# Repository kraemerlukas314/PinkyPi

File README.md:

# PinkyPi
Ortho Staggered ergo split keyboard using Raspberry Pi Pico \
\
 \
\

# Flash CircuitPython firmware:
0. Connect Pico to PC while holding down the "Bootsel" button
1. Open Thonny
2. Go to: Tools -> Options -> Interpreter
3. Choose CircuitPython (RP2040)
4. Click on "Install or update CircuitPython"
5. Rest is self-explanatory, firmware version 9.0.5 is recommended (code is only tested on this version)

# Run the keyboard code:
1. Flash CircuitPython firmware
2. copy "lib" folder of this repo to the Picos internal storage
3. Open Thonny
4. Execute the actual .py code file
5. (rename file to main if it should run automatically on Pico startup)

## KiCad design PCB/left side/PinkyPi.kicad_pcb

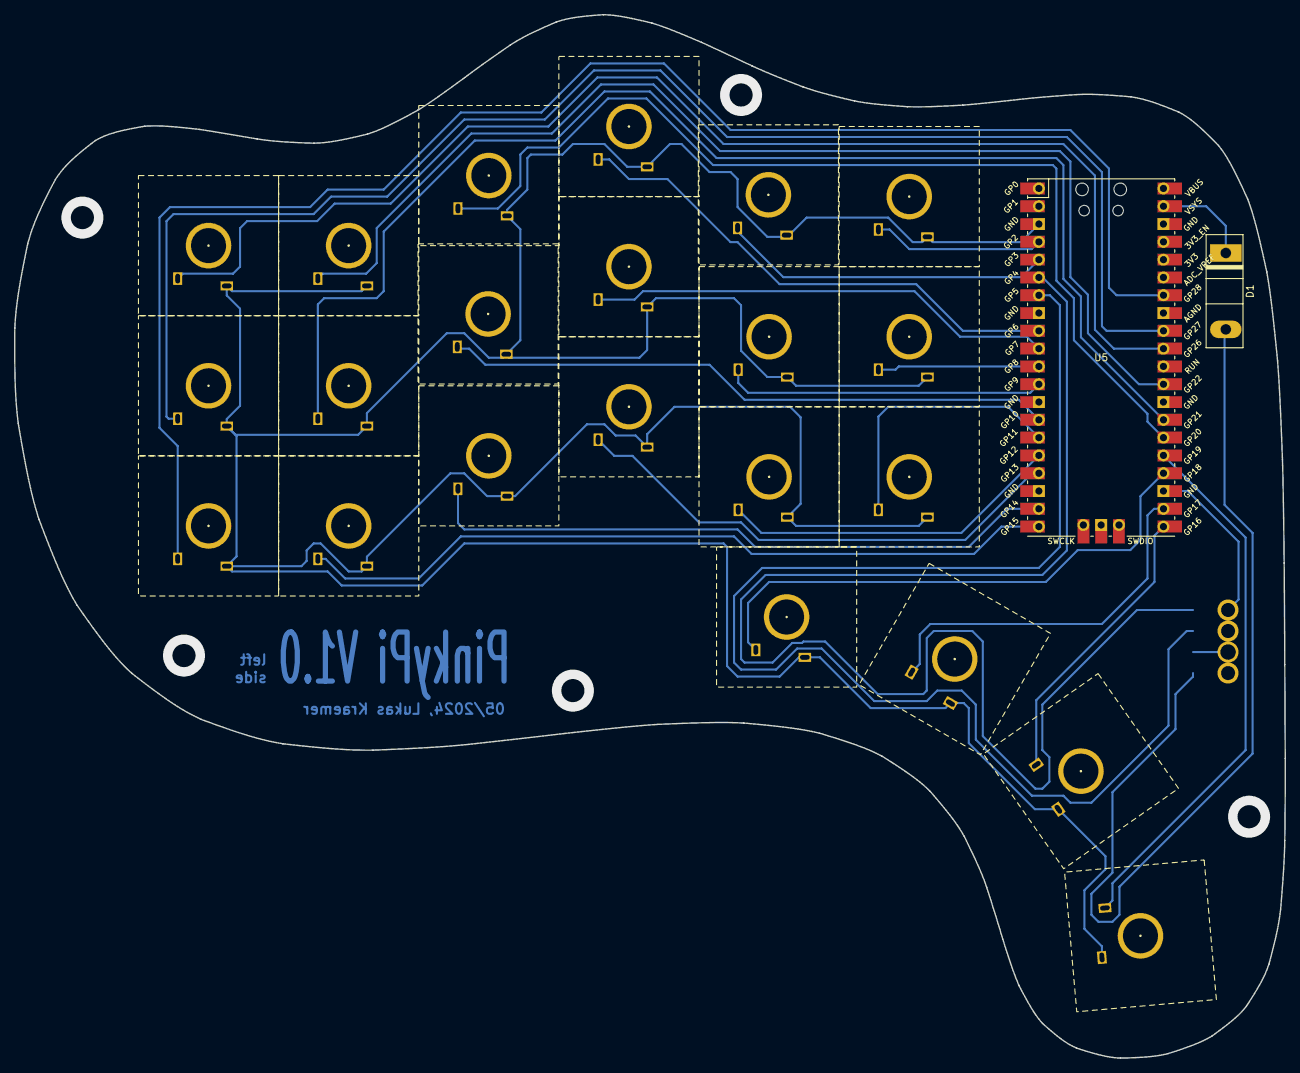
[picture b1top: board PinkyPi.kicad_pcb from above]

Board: 2 copper layers, 181.3 x 148.9 mm, 25 parts (0 on the bottom side), 27 nets.

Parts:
D1: STBR3008WY; D_DO-247_Vertical
U1, U2, U3, U4, U6, U7, U8, U9, U10, U11, U12, U13, U14, U15, U16, U17, U18, U19, U20, U21, U22, U24: Gateron Switch Footprint
U5: Pico; RPi_Pico_SMD_TH
U23: Communication Port

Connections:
/L1: U1.2 (OUT), U5.4 (GPIO2)
/L2: U5.5 (GPIO3), U7.2 (OUT)
/L3: U5.9 (GPIO6), U12.2 (OUT)
/L4: U2.2 (OUT), U5.10 (GPIO7)
/L5: U5.11 (GPIO8), U8.2 (OUT)
/L6: U5.12 (GPIO9), U13.2 (OUT)
/L7: U5.32 (GPIO27_ADC1), U18.2 (OUT)
/L8: U5.14 (GPIO10), U9.2 (OUT)
/L9: U5.15 (GPIO11), U14.2 (OUT)
/L10: U4.2 (OUT), U5.16 (GPIO12)
/L11: U5.17 (GPIO13), U10.2 (OUT)
/L12: U5.34 (GPIO28_ADC2), U20.2 (OUT)
/L13: U5.19 (GPIO14), U6.2 (OUT)
/L14: U5.20 (GPIO15), U11.2 (OUT)
/L15: U5.21 (GPIO16), U17.2 (OUT)
/L16: U5.24 (GPIO18), U16.2 (OUT)
/L17: U5.25 (GPIO19), U19.2 (OUT)
/L18: U5.26 (GPIO20), U15.2 (OUT)
/L19: U3.2 (OUT), U5.27 (GPIO21)
/L20: U5.29 (GPIO22), U22.2 (OUT)
/L21: U5.31 (GPIO26_ADC0), U21.2 (OUT)
/L22: U5.22 (GPIO17), U24.2 (OUT)
GND: U1.1 (IN), U2.1 (IN), U3.1 (IN), U4.1 (IN), U5.3 (GND), U5.8 (GND), U5.13 (GND), U5.18 (GND), U5.23 (GND), U5.28 (GND), U5.38 (GND), U6.1 (IN), U7.1 (IN), U8.1 (IN), U9.1 (IN), U10.1 (IN), U11.1 (IN), U12.1 (IN), U13.1 (IN), U14.1 (IN), U15.1 (IN), U16.1 (IN), U17.1 (IN), U18.1 (IN), U19.1 (IN), U20.1 (IN), U21.1 (IN), U22.1 (IN), U23.2 (GND), U24.1 (IN)
unnamed: D1.2 (A), U23.1 (VCC)
unnamed: D1.1 (K), U5.39 (VSYS)
unnamed: U5.7 (GPIO5), U23.3 (RX)
unnamed: U5.6 (GPIO4), U23.4 (TX)

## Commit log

2024-05-03 inital commit
2024-05-03 added images, first test program
2024-05-04 added PCB left
2024-06-29 own communication protocol working
2024-06-29 update docs
2024-06-29 communication
2024-06-30 savety commit before change of protocol
2024-07-04 not working
2024-07-05 working communication!
2024-07-05 right half working, left sending key presses
2024-07-05 MVP working
2024-07-06 working using two USB cables
2024-07-06 layout changes
2024-07-10 add docs
2024-07-12 added docs2
2024-07-12 added image
